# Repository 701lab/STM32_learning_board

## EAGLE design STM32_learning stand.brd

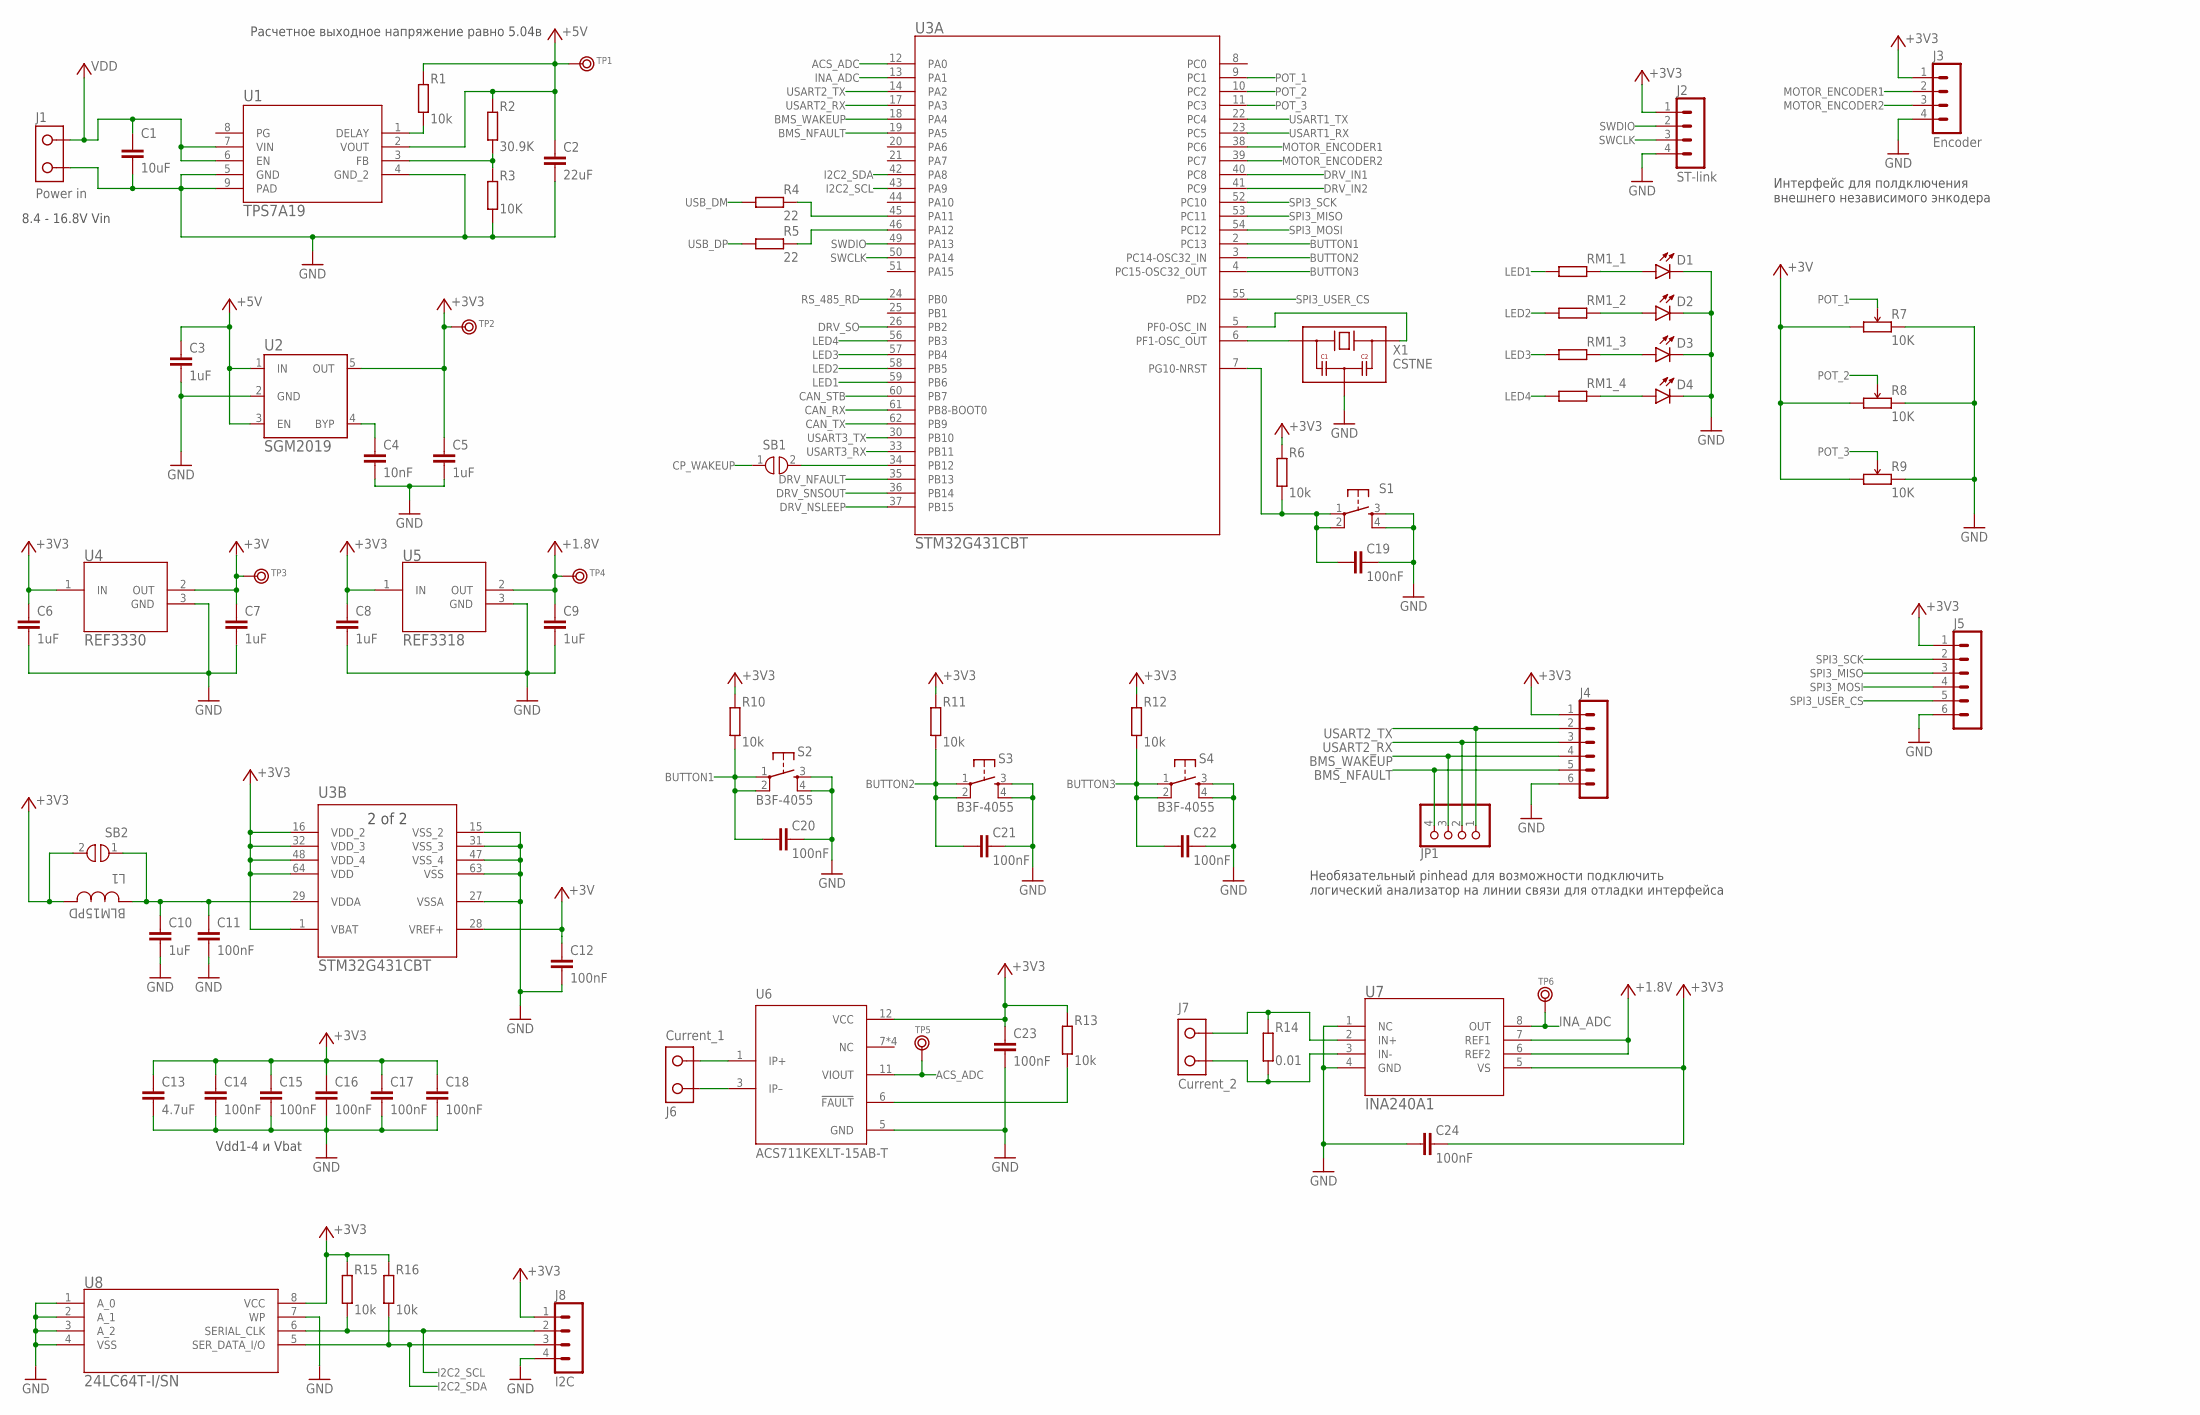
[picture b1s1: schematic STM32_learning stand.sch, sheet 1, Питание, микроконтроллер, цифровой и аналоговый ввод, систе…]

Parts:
C1: 10uF; C1206
C2: 22uF; C0805
C3, C5, C6, C7, C8, C9, C10: 1uF; C0603
C4: 10nF; C0402
C11, C12, C14, C15, C16, C17, C18, C19, C20, C21, C22, C23, C24: 100nF; C0402
C13: 4.7uF; C0603
D1, D2, D3, D4: Blue; LED-0805
J1: Power in; DG301-2P
J2: ST-link; S4B-PH-K
J3: Encoder; S4B-PH-K
J4: BMS_interface; S6B-PH-K
J5: S6B-PH-K
J6: Current_1; DG301-2P
J7: Current_2; DG301-2P
J8: I2C; B4B-PH-K
JP1: PINHD-1X4; 1X04
L1: BLM15PD; 0402
R1, R6, R10, R11, R12, R13, R15, R16: 10k; R0402
R2: 30.9K; R0603
R3: 10K; R0603
R4, R5: 22; R0402
R7, R8, R9: 10K; ALPS_PTM
R14: 0.01; CS_R0805
RM1: RES_ARRAY; 0603-ARC
S1: MOMENTARY-SWITCH-SPST-2-[SMD-5.2MM]; TACTILE_SWITCH_SMD_5.2MM
S2, S3, S4: B3F-4055; SWITCH_B3F-4055
SB1, SB2: SOLDER_BRIDGE
TP1, TP2, TP3, TP4, TP5, TP6: TEST_RING
U1: TPS7A19; DRB0008B
U2: SGM2019; SOT23-5
U3: STM32G431CBT; LQFP64-10X10MM
U4: REF3330; SOT-23-3
U5: REF3318; SOT-23-3
U6: ACS711KEXLT-15AB-T; SENSOR_ACS711KEXLT-15AB-T
U7: INA240A1; TSSOP-8
U8: 24LC64T-I/SN; SOIC8
X1: CSTNE; MURATA_SMD_3P

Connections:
+1.8V: C9.2, TP4.1, U5.2 (OUT), U7.6 (REF2), U7.7 (REF1)
+3V: C7.2, C12.1, R7.P$1 (1), R8.P$1 (1), R9.P$1 (1), TP3.1, U3.28 (VREF+), U4.2 (OUT)
+3V3: C5.2, C6.2, C8.2, C13.2, C14.1, C15.1, C16.1, C17.1, C18.1, C23.1, C24.2, J2.1, J3.1, J4.1, J5.1, J8.1, L1.2, R6.2, R10.2, R11.2, R12.2, R13.2, R15.2, R16.2, SB2.2, TP2.1, U2.5 (OUT), U3.1 (VBAT), U3.16 (VDD_2), U3.32 (VDD_3), U3.48 (VDD_4), U3.64 (VDD), U4.1 (IN), U5.1 (IN), U6.12 (VCC), U7.5 (VS), U8.8 (VCC); also elsewhere on the board
+5V: C2.1, C3.2, R1.2, R2.2, TP1.1, U1.2 (VOUT), U2.1 (IN), U2.3 (EN); also elsewhere on the board
ACS_ADC: TP5.1, U3.12 (PA0), U6.11 (VIOUT)
ACS_IP+: J6.1, U6.1 (IP+)
ACS_IP-: J6.2, U6.3 (IP–)
BMS_NFAULT: J4.5, JP1.4, U3.19 (PA5)
BMS_WAKEUP: J4.4, JP1.3, U3.18 (PA4)
BUTTON1: C20.1, R10.1, S2.1, S2.2, U3.2 (PC13)
BUTTON2: C21.1, R11.1, S3.1, S3.2, U3.3 (PC14-OSC32_IN)
BUTTON3: C22.1, R12.1, S4.1, S4.2, U3.4 (PC15-OSC32_OUT)
CAN_RX: U3.61 (PB8-BOOT0); also elsewhere on the board
CAN_STB: U3.60 (PB7); also elsewhere on the board
CAN_TX: U3.62 (PB9); also elsewhere on the board
CP_WAKEUP: SB1.1; also elsewhere on the board
DRV_IN1: U3.40 (PC8); also elsewhere on the board
DRV_IN2: U3.41 (PC9); also elsewhere on the board
DRV_NFAULT: U3.35 (PB13); also elsewhere on the board
DRV_NSLEEP: U3.37 (PB15); also elsewhere on the board
DRV_SNSOUT: U3.36 (PB14); also elsewhere on the board
DRV_SO: U3.26 (PB2); also elsewhere on the board
GND: C1.2, C2.2, C3.1, C4.2, C5.1, C6.1, C7.1, C8.1, C9.1, C10.1, C11.2, C12.2, C13.1, C14.2, C15.2, C16.2, C17.2, C18.2, C19.2, C20.2, C21.2, C22.2, C23.2, C24.1, D1.- (C), D2.- (C), D3.- (C), D4.- (C), J1.1, J2.4, J3.4, J4.6, J5.6, J8.4, R3.1, R7.P$3 (3), R8.P$3 (3), R9.P$3 (3), S1.3, S1.4, S2.3, S2.4, S3.3, S3.4, S4.3, S4.4, U1.4 (GND_2), U1.5 (GND), U1.9 (PAD), U2.2 (GND), U3.15 (VSS_2), U3.27 (VSSA), U3.31 (VSS_3), U3.47 (VSS_4), U3.63 (VSS), U4.3 (GND), U5.3 (GND), U6.5 (GND), U7.1 (NC), U7.4 (GND), U8.1 (A_0), U8.2 (A_1), U8.3 (A_2), U8.4 (VSS), U8.7 (WP), X1.2 (GND); also elsewhere on the board
I2C2_SCL: J8.2, R15.1, U3.43 (PA9), U8.6 (SERIAL_CLK)
I2C2_SDA: J8.3, R16.1, U3.42 (PA8), U8.5 (SER_DATA_I/O)
INA_ADC: TP6.1, U3.13 (PA1), U7.8 (OUT)
LED1: RM1.1, U3.59 (PB6)
LED2: RM1.2 (1), U3.58 (PB5)
LED3: RM1.3 (1), U3.57 (PB4)
LED4: RM1.4 (1), U3.56 (PB3)
MOTOR_ENCODER1: J3.2, U3.38 (PC6)
MOTOR_ENCODER2: J3.3, U3.39 (PC7)
unnamed: D4.+ (A), RM1.5 (2)
unnamed: SB1.2, U3.34 (PB12)
unnamed: C4.1, U2.4 (BYP)
unnamed: D3.+ (A), RM1.6 (2)
unnamed: R4.2, U3.45 (PA11)
unnamed: R5.2, U3.46 (PA12)
unnamed: D2.+ (A), RM1.7 (2)
unnamed: D1.+ (A), RM1.8 (2)
unnamed: U3.6 (PF1-OSC_OUT), X1.1 (IN)
unnamed: U3.5 (PF0-OSC_IN), X1.3 (OUT)
unnamed: C19.1, R6.1, S1.1, S1.2, U3.7 (PG10-NRST)
unnamed: R2.1, R3.2, U1.3 (FB)
unnamed: R1.1, U1.1 (DELAY)
unnamed: R13.1, U6.6 (!FAULT)
unnamed: J7.1, R14.2, U7.2 (IN+)
unnamed: J7.2, R14.1, U7.3 (IN-)
POT_1: R7.P$2 (2), U3.9 (PC1)
POT_2: R8.P$2 (2), U3.10 (PC2)
POT_3: R9.P$2 (2), U3.11 (PC3)
RS_485_RD: U3.24 (PB0); also elsewhere on the board
SPI3_MISO: J5.3, U3.53 (PC11)
SPI3_MOSI: J5.4, U3.54 (PC12)
SPI3_SCK: J5.2, U3.52 (PC10)
SPI3_USER_CS: J5.5, U3.55 (PD2)
SWCLK: J2.3, U3.50 (PA14)
SWDIO: J2.2, U3.49 (PA13)
USART1_RX: U3.23 (PC5); also elsewhere on the board
USART1_TX: U3.22 (PC4); also elsewhere on the board
USART2_RX: J4.3, JP1.2, U3.17 (PA3)
USART2_TX: J4.2, JP1.1, U3.14 (PA2)
USART3_RX: U3.33 (PB11); also elsewhere on the board
USART3_TX: U3.30 (PB10); also elsewhere on the board
USB_DM: R4.1; also elsewhere on the board
USB_DP: R5.1; also elsewhere on the board
VDD: C1.1, J1.2, U1.6 (EN), U1.7 (VIN); also elsewhere on the board
VDDA: C10.2, C11.1, L1.1, SB2.1, U3.29 (VDDA)

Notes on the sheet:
Необязательный pinhead для возможности подключить логический анализатор на линии связи для отладки интерфейса
Интерфейс для полдключения внешнего независимого энкодера
Расчетное выходное напряжение равно 5.04в
Vdd1-4 и Vbat
8.4 - 16.8V Vin

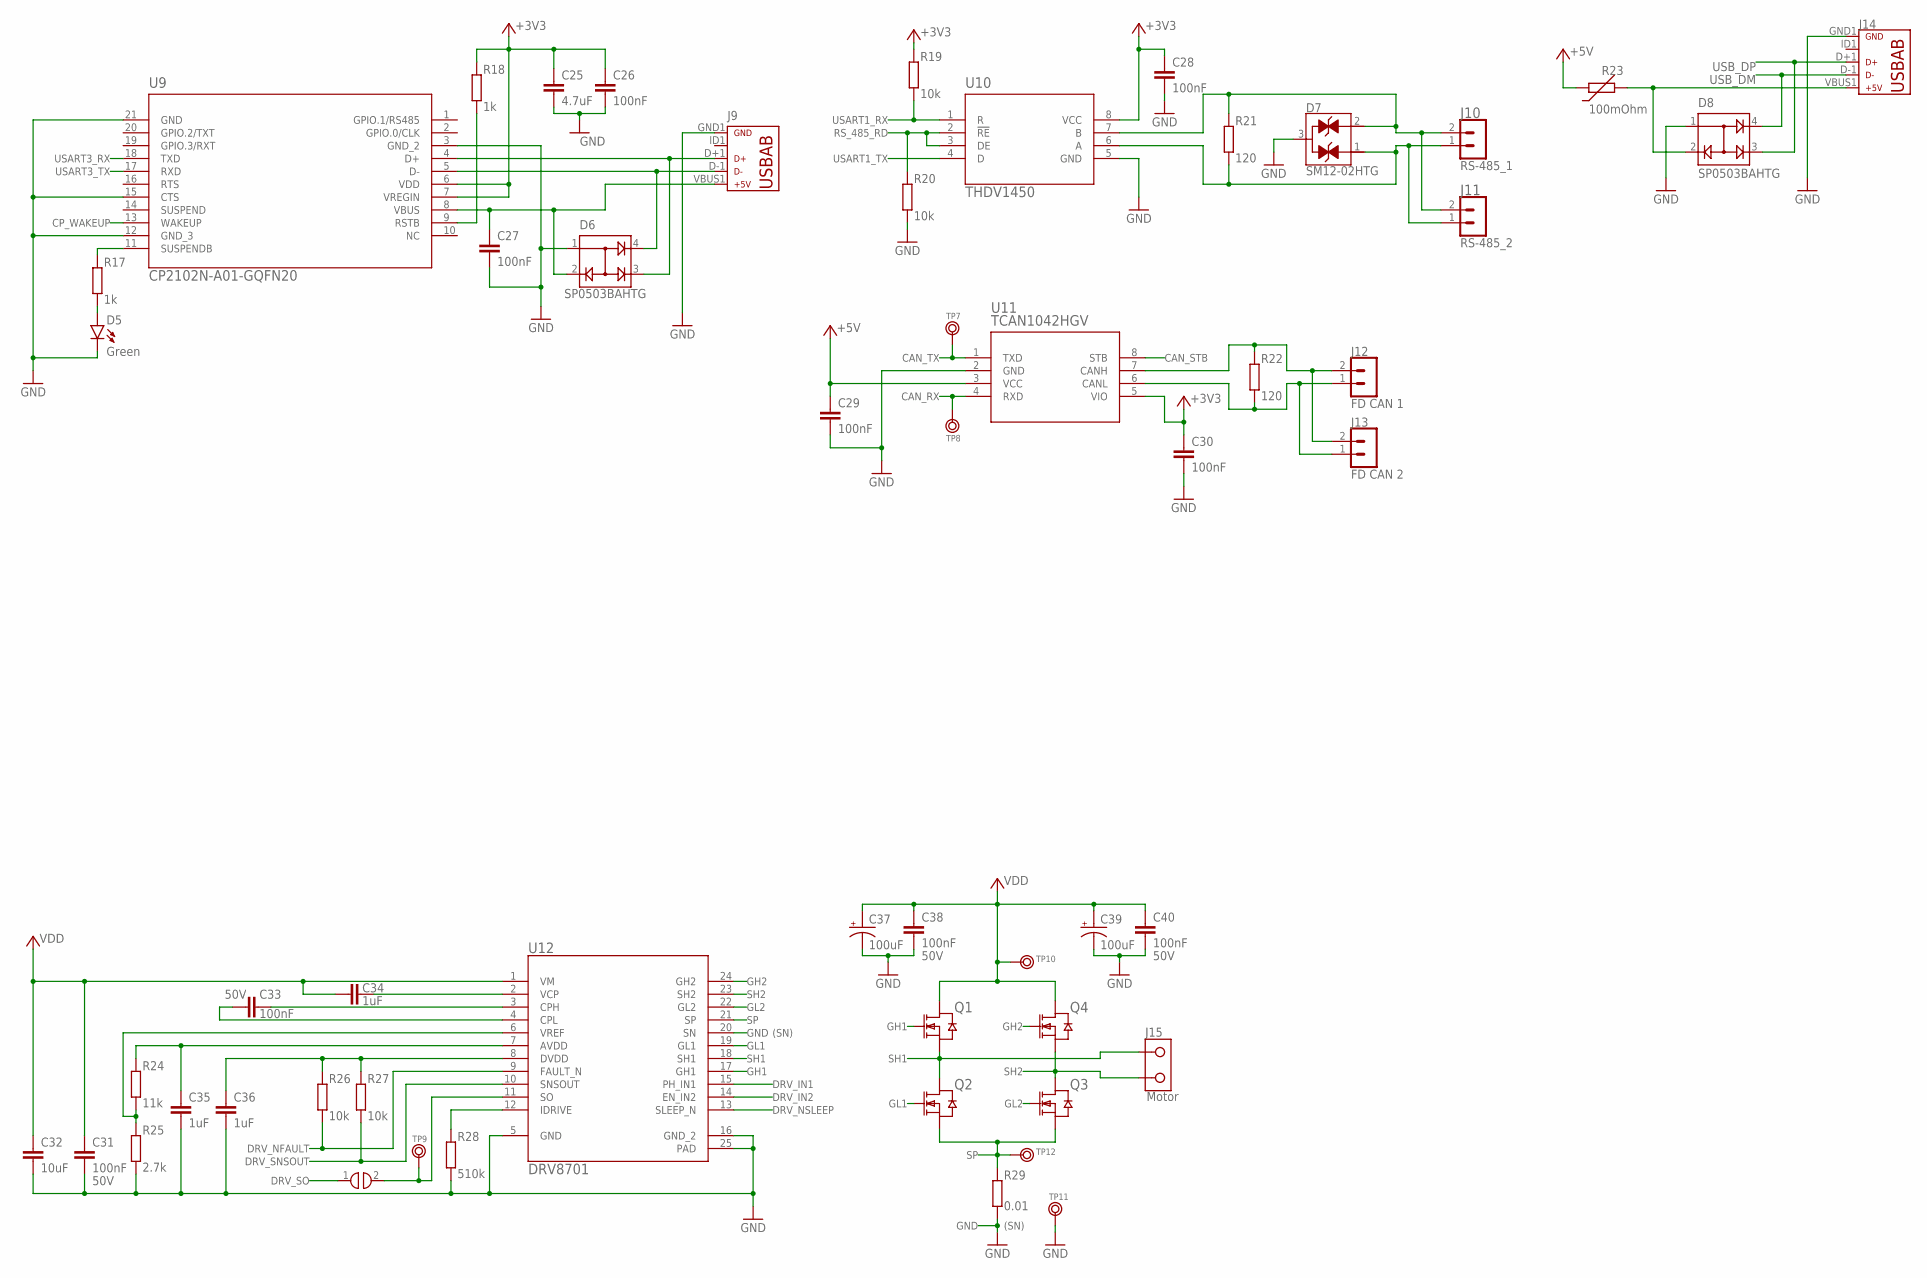
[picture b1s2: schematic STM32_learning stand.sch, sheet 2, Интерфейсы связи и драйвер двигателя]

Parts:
C25: 4.7uF; C0603
C26, C27, C28, C29, C30: 100nF; C0402
C31, C33, C38, C40: 100nF; C0603
C32: 10uF; C1206
C34, C35, C36: 1uF; C0603
C37, C39: 100uF; 6.3X7.7
D5: Green; LED-0805
D6, D8: SP0503BAHTG; SOT143
D7: SM12-02HTG; SOT23
J9, J14: USB_MICRO""; USB-MICRO-SMD
J10: RS-485_1; S2B-PH-K
J11: RS-485_2; S2B-PH-K
J12: FD CAN 1; S2B-PH-K
J13: FD CAN 2; S2B-PH-K
J15: Motor; DG301-2P
Q1, Q2, Q3, Q4: SON5X6_MOSFET; SON5X6
R17, R18: 1k; R0402
R19, R20, R26, R27: 10k; R0402
R21, R22: 120; R0805
R23: 100mOhm; 0805_PTC_FUSE
R24: 11k; R0402
R25: 2.7k; R0402
R28: 510k; R0402
R29: 0.01; CS_R0805
SB3: SOLDER_BRIDGE
TP7, TP8, TP9, TP10, TP11, TP12: TEST_RING
U9: CP2102N-A01-GQFN20; QFN20C_3X3
U10: THDV1450; SOIC8
U11: TCAN1042HGV; SOIC_8
U12: DRV8701; VQFN-24

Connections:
+3V3: C25.2, C26.1, C28.1, C30.1, R18.2, R19.2, U9.6 (VDD), U9.7 (VREGIN), U10.8 (VCC), U11.5 (VIO); also elsewhere on the board
+5V: C29.1, R23.1, U11.3 (VCC); also elsewhere on the board
CANH: J12.2, J13.2, R22.1, U11.7 (CANH)
CANL: J12.1, J13.1, R22.2, U11.6 (CANL)
CAN_RX: TP8.1, U11.4 (RXD); also elsewhere on the board
CAN_STB: U11.8 (STB); also elsewhere on the board
CAN_TX: TP7.1, U11.1 (TXD); also elsewhere on the board
CP_WAKEUP: U9.13 (WAKEUP); also elsewhere on the board
DRV_IN1: U12.15 (PH_IN1); also elsewhere on the board
DRV_IN2: U12.14 (EN_IN2); also elsewhere on the board
DRV_NFAULT: R26.1, U12.9 (FAULT_N); also elsewhere on the board
DRV_NSLEEP: U12.13 (SLEEP_N); also elsewhere on the board
DRV_SNSOUT: R27.1, U12.10 (SNSOUT); also elsewhere on the board
DRV_SO: SB3.1; also elsewhere on the board
GH1: Q1.4 (G), U12.17 (GH1)
GH2: Q4.4 (G), U12.24 (GH2)
GL1: Q2.4 (G), U12.19 (GL1)
GL2: Q3.4 (G), U12.22 (GL2)
GND: C25.1, C26.2, C27.2, C28.2, C29.2, C30.2, C31.2, C32.2, C35.1, C36.1, C37.2 (-), C38.2, C39.2 (-), C40.2, D5.- (C), D6.1, D7.3, D8.1, J9.GND1 (GND), J14.GND1 (GND), R20.1, R25.1, R28.1, R29.1, TP11.1, U9.3 (GND_2), U9.12 (GND_3), U9.15 (CTS), U9.21 (GND), U10.5 (GND), U11.2 (GND), U12.5 (GND), U12.16 (GND_2), U12.20 (SN), U12.25 (PAD); also elsewhere on the board
unnamed: D6.3, J9.D+1 (D+), U9.4 (D+)
unnamed: D6.4, J9.D-1 (D-), U9.5 (D-)
unnamed: C27.1, D6.2, J9.VBUS1 (VBUS), U9.8 (VBUS)
unnamed: R17.2, U9.11 (SUSPENDB)
unnamed: R18.1, U9.9 (RSTB)
unnamed: D5.+ (A), R17.1
unnamed: D8.2, J14.VBUS1 (VBUS), R23.2
unnamed: D7.2, J10.2, J11.2, R21.2, U10.7 (B)
unnamed: D7.1, J10.1, J11.1, R21.1, U10.6 (A)
unnamed: C33.1, U12.3 (CPH)
unnamed: SB3.2, TP9.1, U12.11 (SO)
unnamed: C33.2, U12.4 (CPL)
unnamed: C34.2, U12.2 (VCP)
unnamed: R24.1, R25.2, U12.6 (VREF)
unnamed: C35.2, R24.2, U12.7 (AVDD)
unnamed: C36.2, R26.2, R27.2, U12.8 (DVDD)
unnamed: R28.2, U12.12 (IDRIVE)
RS_485_RD: R20.2, U10.2 (!RE), U10.3 (DE); also elsewhere on the board
SH1: J15.1, Q1.1 (S), Q1.2 (S), Q1.3 (S), Q2.5 (D), Q2.6 (D), Q2.7 (D), Q2.8 (D), Q2.9 (D), U12.18 (SH1)
SH2: J15.2, Q3.5 (D), Q3.6 (D), Q3.7 (D), Q3.8 (D), Q3.9 (D), Q4.1 (S), Q4.2 (S), Q4.3 (S), U12.23 (SH2)
SP: Q2.1 (S), Q2.2 (S), Q2.3 (S), Q3.1 (S), Q3.2 (S), Q3.3 (S), R29.2, TP12.1, U12.21 (SP)
USART1_RX: R19.1, U10.1 (R); also elsewhere on the board
USART1_TX: U10.4 (D); also elsewhere on the board
USART3_RX: U9.18 (TXD); also elsewhere on the board
USART3_TX: U9.17 (RXD); also elsewhere on the board
USB_DM: D8.4, J14.D-1 (D-); also elsewhere on the board
USB_DP: D8.3, J14.D+1 (D+); also elsewhere on the board
VDD: C31.1, C32.1, C34.1, C37.1 (+), C38.1, C39.1 (+), C40.1, Q1.5 (D), Q1.6 (D), Q1.7 (D), Q1.8 (D), Q1.9 (D), Q4.5 (D), Q4.6 (D), Q4.7 (D), Q4.8 (D), Q4.9 (D), TP10.1, U12.1 (VM); also elsewhere on the board

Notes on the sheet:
(SN)
50V

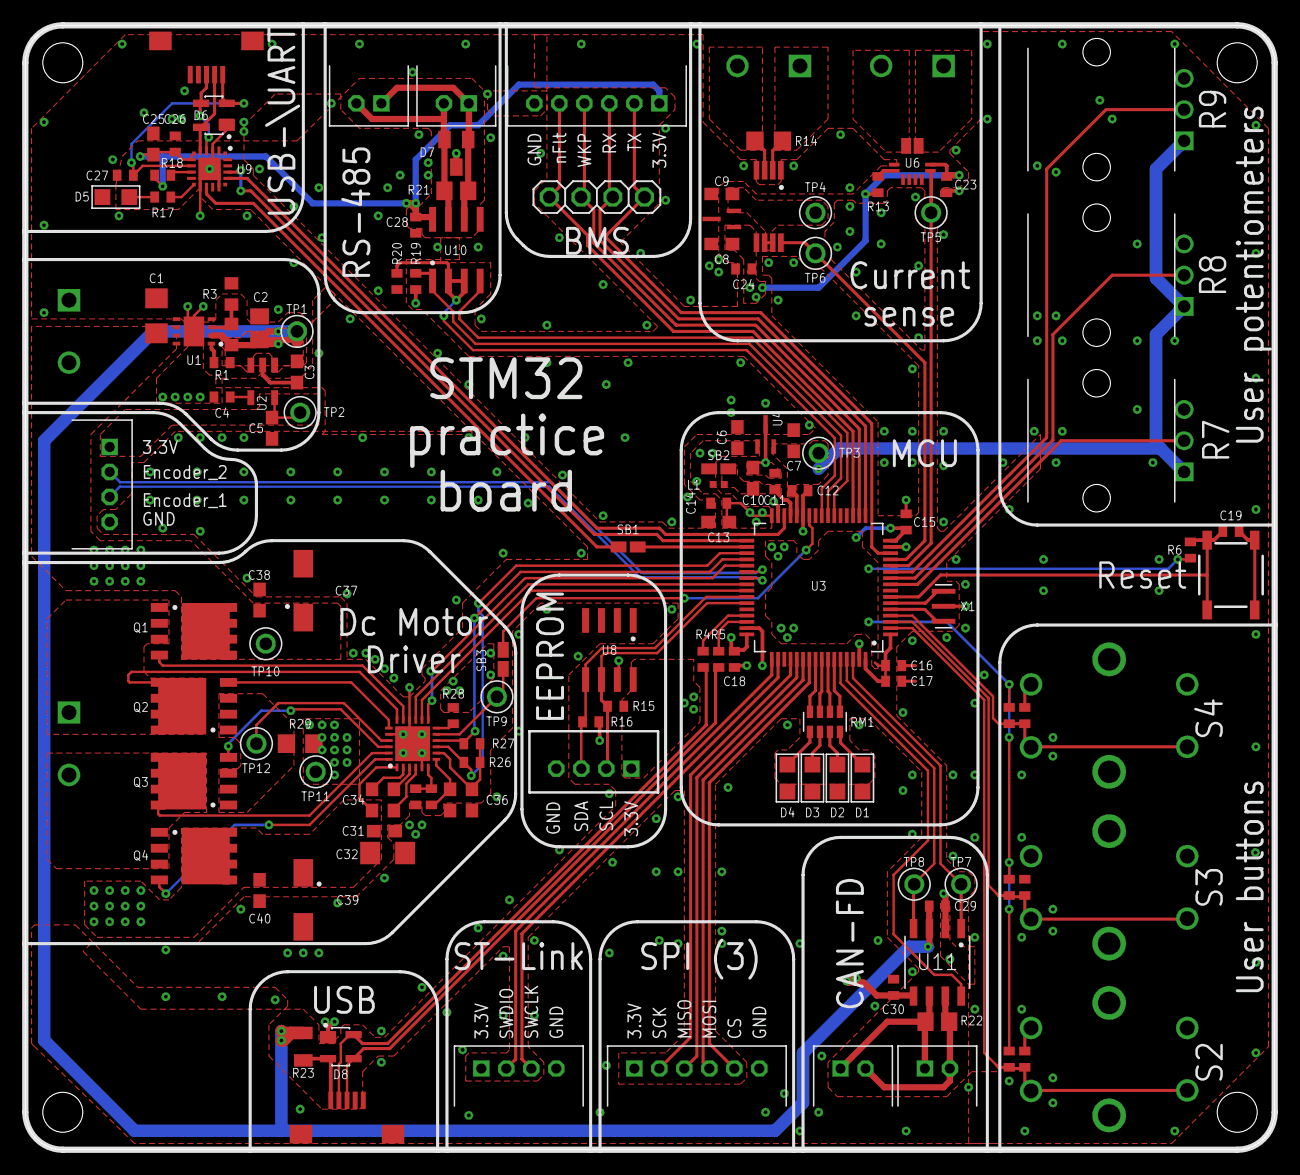
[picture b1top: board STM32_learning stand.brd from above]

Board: 2 copper layers, 100.0 x 90.0 mm, 131 parts (0 on the bottom side), 94 nets.

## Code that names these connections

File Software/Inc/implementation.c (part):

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// ******** MCU connections overview ******** //
/*
	LEDs:
		PB3-PB6 (digital outputs);

	FD CAN (TCAN1042HGV) :
		PB7 - STB (digital output) - TCAN standby pin;
		PB8-9 - RX and TX respectively (FDCAN1, alternate function 9);

	User SPI:
		PC10-PC12 - SCK, MISO, MOSI respectively (SPI3, alternate function 6);
		PD2 - CS (digital output) - user SPI chip select;

	USB:
		PA11-PA12 - DM and DP respectively (alternate function ?? idk if it even an alternate function);

	EEPROM:
		PA8-PA9 - SDA and SCL respectively (I2C2, alternate function 4);

	Motor driver (DRV8701P):
		PC8-PC9 - IN1 and IN2 respectively (TIM8 PWM CH3-4, alternate function 4) - driver control pins;
		PB13 - nFault (digital input, external interrupt) - pulled logic low with fault condition;
		PB14 - SNSOUT (digital input, external interrupt) - pulled logic low when the drive current hits the current chopping threshold;
		PB15 - nSleep (digital output) - Pull logic low to put device into a low-power sleep mode with FETs High-Z;
		PB2 - SO (ADC2 IN12) - Voltage on this pin is equal to the SP voltage times AV plus an offset;

	Motor encoder:
		PC6-7 - encoder input 1 and 2 respectively (TIM3 encoder mode Ch1-2, alternate function 2);

	USB-UART (CP2102N-A01-GQFN20R):
		PB10-11 - TX and RX respectively (UART3, alternate function 7);
		PB12 - wakeup  (input or output ??) -  Remote USB wakeup interrupt input:

	RS-485 (THDV1450):
		PC4-5 - TX and RX respectively (UART1, alternate function 7);
		PB0 - RW (digital output) - control recieve and transmit mode of the device. "1" - transiver, "0" - receiver;

	BMS interface:
		PA2-3 - TX and RX respectively (UART2, alternate function 7);
		PA4 - wakeup (digital output) - ... wakes up BMS;
		PA5 - nFault (digital input, external interrupt) -  Pulled logic low with fault condition;

	User buttons:
		PC13-PC15 - button 1 to 3 respectively (digital input);

	User potentiometers:
		PC1-3 - potentiometers 1 to 3 respectively (ADC1 IN7-9 respectively)

	Current sensor (ACS711KEXLT-15AB-T):
		PA0 - VIOut (ADC1 IN1) - Voltage proportional to the flowing current;

	Current sensor (INA240A1PW):
		PA1 - OUT (ADC1 IN2) - Voltage proportional to the flowing current;

	TIM15 - counts time with 0.1 ms precision for mistakes log

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
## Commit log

2020-02-27 small update
2020-05-12 Initialized project to develope software
2020-05-12 deleted unnecessary assembly drawing
2020-05-12 init all main files for further development
2020-05-12 finished peripherial explanation
2020-05-13 Added but not tested clock setups
2020-05-13 timers setup half finished and half tested
2020-05-13 Finished all timers setup for now, added UART2 data transmittion
2020-05-15 CAN is working in test mode, but there are still tons of work
2020-05-17 final CAN commit before robots board v2.0
2020-05-18 added SPI read
2020-05-18 ADC almost ready
2020-05-18 ADC is working now
2020-05-19 Added calibration and better current measurement organiztion
2020-05-20 Tested current sencing and calibrated ina240 scale
2020-05-20 added motor control

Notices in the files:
parts and their libraries:
con-jst-ph: Copyright (C) 2016, Bob Starr
COPYRIGHT: Copyright (C) 2018 Accelerated Designs. All rights reserved
COPYRIGHT: Copyright (C) 2016 Accelerated Designs. All rights reserved
